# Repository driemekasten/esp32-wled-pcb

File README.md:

# ESP32-WLED-PCB

This is a small (18,70 x 26 mm) pcb for WLED based on a ESP32-PICO-D4 MCU.

## License
[Creative Commons Attribution-NonCommercial-ShareAlike 4.0 International](https://creativecommons.org/licenses/by-nc-sa/4.0/)

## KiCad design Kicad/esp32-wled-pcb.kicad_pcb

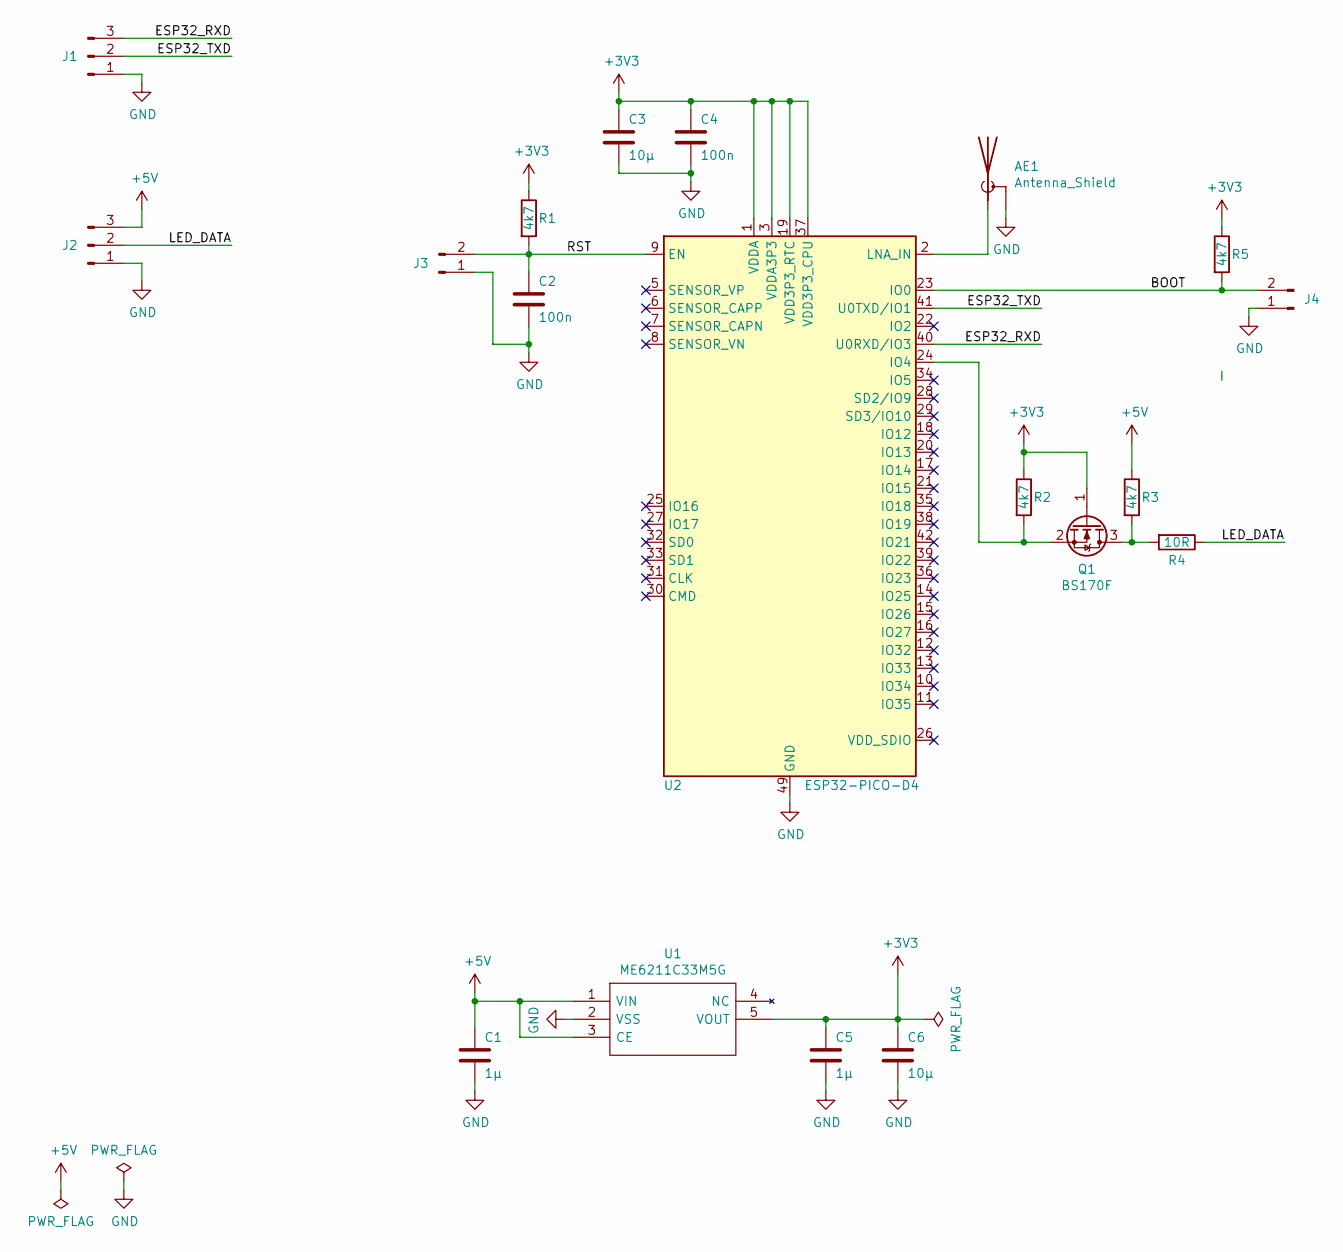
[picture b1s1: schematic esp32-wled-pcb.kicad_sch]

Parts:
AE1: Antenna_Shield; Texas_SWRA117D_2.4GHz_Left
C1, C5: 1µ; C_0805_2012Metric
C2, C4: 100n; C_0805_2012Metric
C3, C6: 10µ; C_0805_2012Metric
J1, J2: Conn_01x03_Male; PinHeader_1x03_P2.54mm_Vertical
J3, J4: SW_Push; PinHeader_1x02_P2.54mm_Vertical
Q1: BS170F; SOT-23
R1, R2, R3, R5: 4k7; R_0805_2012Metric
R4: 10R; R_0805_2012Metric
U1: ME6211C33M5G; SOT95P282X145-5N; Manufacturer_Part_Number ME6211C33M5G
U2: ESP32-PICO-D4; QFN-48-1EP_7x7mm_P0.5mm_EP5.3x5.3mm

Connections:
+3V3: C3.1, C4.1, C5.1, C6.1, Q1.1 (G), R1.1, R2.1, R5.1, U1.5 (VOUT), U2.1 (VDDA), U2.3 (VDDA3P3), U2.4 (VDDA3P3), U2.19 (VDD3P3_RTC), U2.37 (VDD3P3_CPU), U2.43 (VDDA), U2.46 (VDDA)
+5V: C1.1, J2.3, R3.1, U1.1 (VIN), U1.3 (CE)
/BOOT: J4.2, R5.2, U2.23 (IO0)
/ESP32_RXD: J1.3, U2.40 (U0RXD/IO3)
/ESP32_TXD: J1.2, U2.41 (U0TXD/IO1)
/LED_DATA: J2.2, R4.1
/RST: C2.1, J3.2, R1.2, U2.9 (EN)
GND: AE1.2 (Shield), C1.2, C2.2, C3.2, C4.2, C5.2, C6.2, J1.1, J2.1, J3.1, J4.1, U1.2 (VSS), U2.49 (GND)
unnamed: AE1.1 (A), U2.2 (LNA_IN)
unnamed: Q1.2 (S), R2.2, U2.24 (IO4)
unnamed: Q1.3 (D), R3.2, R4.2

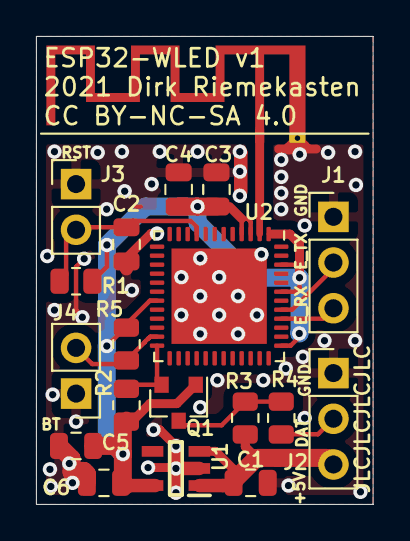
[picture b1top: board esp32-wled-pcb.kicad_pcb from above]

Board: 2 copper layers, 18.7 x 26.0 mm, 19 parts (0 on the bottom side), 11 nets.

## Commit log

2021-10-09 commit initial
2021-10-29 still wip
2021-10-29 add license
2021-11-01 finalize design
2021-11-01 crop pcb png
2021-11-20 fix silkscreen
2021-11-26 add basic readme
2021-11-26 add pcb image
2021-11-26 resize pcb image
2021-11-26 add image to README.MD
2021-11-26 intermediate commit
2021-12-30 save in KiCad 6.0 format

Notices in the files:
Kicad/esp32-wled-pcb.kicad_pcb:
CC BY-NC-SA 4.0
